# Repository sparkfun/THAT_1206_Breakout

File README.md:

SparkFun THAT 1206 Breakout
========================================

[*BOB-14002*](https://www.sparkfun.com/products/14002)

The SparkFun THAT 1206 InGenius Breakout Board offers an easy solution to adding a balanced audio input to your circuits. The THAT InGenius technology has been designed for high-grade analog line receiving and offers a low distortion and high common mode rejection in real-world audio applications. Each breakout board combines the THAT 1206 IC, its supporting components, and a ¼" TRS (Tip Ring Sleeve) socket. With these powers combined, you will find it very easy to use the input drivers on breadboards and in projects!

The THAT 1206 InGenius Breakout and its sibling, the THAT 1646 OutSmarts Breakout, perform mirror-image signal conversion. While the OutSmarts is an unbalanced-to-balanced output driver, this InGenius is a balanced-to-unbalanced input receiver. We have made sure to break out each pin you need to utilize the InGenius board, including the unbalanced output (OUT), the positive and negative power supply rails (V+, V-) and, of course, ground (GND). Additionally, adjacent to each leg of the socket are test points for the signal (T, R, S) and normal (TN, RN, SN) contacts.

Repository Contents
-------------------

* **/Hardware** - Eagle design files (.brd, .sch)
* **/Production** - Production panel files (.brd)

Documentation
--------------
* **[Hookup Guide](https://learn.sparkfun.com/tutorials/that-ingenuis-and-outsmarts-breakout-hookup-guide)** - Basic hookup guide for the THAT 1206 and 1646 breakouts.
* **[SparkFun Fritzing repo](https://github.com/sparkfun/Fritzing_Parts)** - Fritzing diagrams for SparkFun products.
* **[SparkFun 3D Model repo](https://github.com/sparkfun/3D_Models)** - 3D models of SparkFun products.

Product Versions
----------------
* [BOB-14002](https://www.sparkfun.com/products/14002) - THAT 1206 InGenius breakout board.
* [BOB-14003](https://www.sparkfun.com/products/14003) - The companion THAT 1646 OutSmarts breakout board.

Version History
---------------
* [V1.0 Tag](https://github.com/sparkfun/THAT_1206_Breakout/commit/8fa3e24b62fe93f8f912508c355df1751a37f655) - Files as of product launch.

License Information
-------------------

This product is _**open source**_!

Please review the LICENSE.md file for license information.

If you have any questions or concerns on licensing, please contact techsupport@sparkfun.com.

Distributed as-is; no warranty is given.

- Your friends at SparkFun.

_<COLLABORATION CREDIT>_

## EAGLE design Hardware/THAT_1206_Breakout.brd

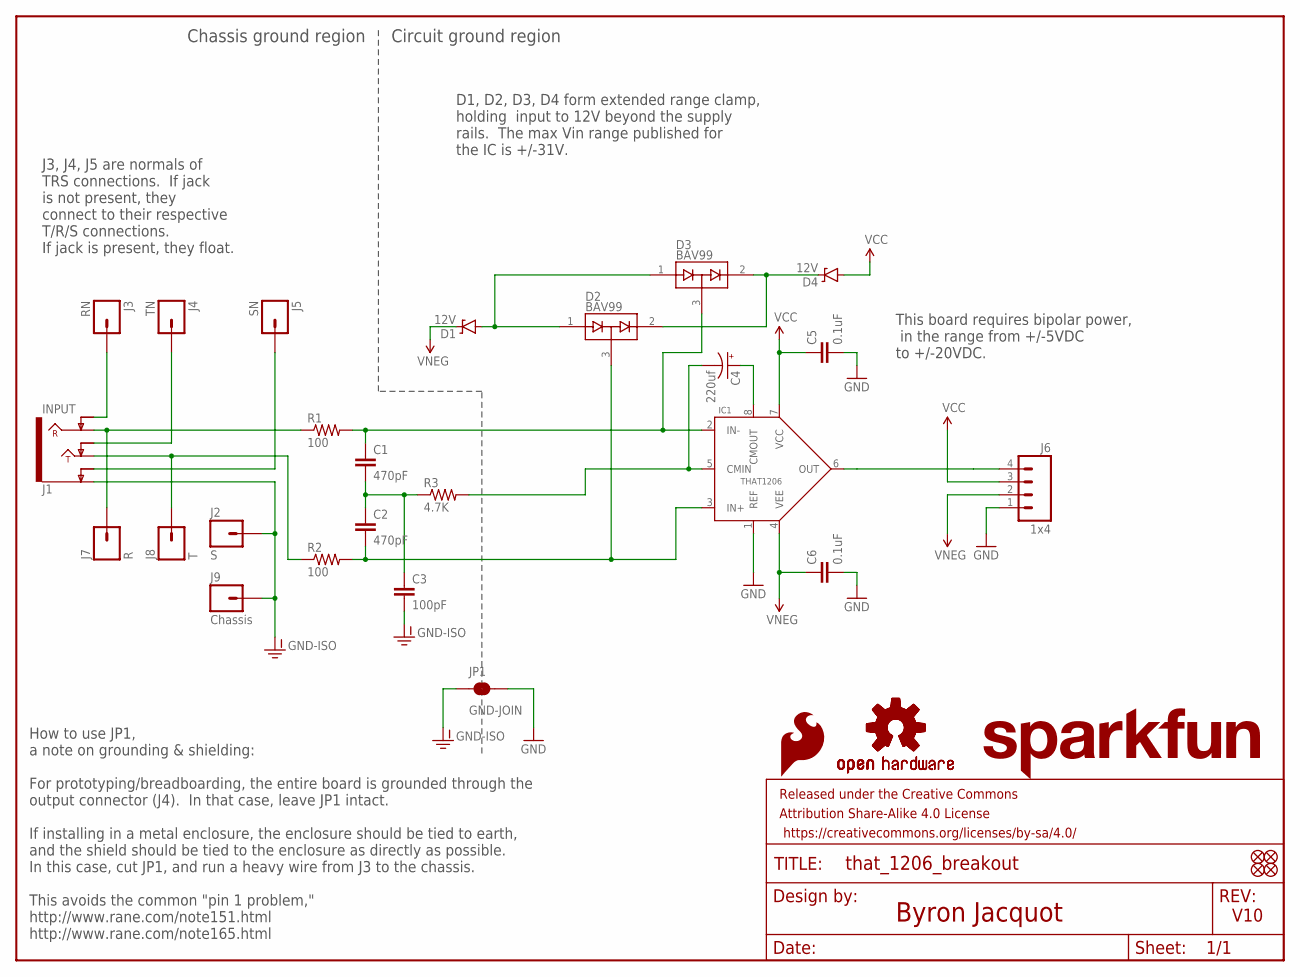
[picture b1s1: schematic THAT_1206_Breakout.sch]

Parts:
C1, C2: 470pF; 0603-CAP
C3: 100pF; 0603-CAP
C4: 220uf; PANASONIC_D
C5, C6: 0.1uF; 0603-CAP
D1, D4: 12V; SOD-323
D2, D3: BAV99; SOT23-3
FD1, FD2, FD3, FD4: FIDUCIALUFIDUCIAL; MICRO-FIDUCIAL
FRAME1: FRAME-LETTER; CREATIVE_COMMONS
IC1: THAT1206; SO08
J1: INPUT; AUDIO_JACK_0.25"_TRS_PTH_RA
J2: S; 1X01_NO_SILK
J3: RN; 1X01_NO_SILK
J4: TN; 1X01_NO_SILK
J5: SN; 1X01_NO_SILK
J6: 1x4; 1X04_NO_SILK_ALL_ROUND
J7: R; 1X01_NO_SILK
J8: T; 1X01_NO_SILK
J9: Chassis; 1X01_NO_SILK
JP1: GND-JOIN; PAD-JUMPER-2-NC_BY_TRACE_YES_SILK
LOGO2: SFE_LOGO_FLAME.2_INCH; SFE_LOGO_FLAME_.2
LOGO3, LOGO4: OSHW-LOGOS; OSHW-LOGO-S
LOGO5: SFE_LOGO_NAME.1_INCH; SFE_LOGO_NAME_.1
R1, R2: 100; 0603-RES
R3: 4.7K; 0603-RES

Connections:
GND: C5.2, C6.2, IC1.1 (REF), J6.1, JP1.2
GND-ISO: C3.2, J1.SLEEVE (EARTH), J2.1, J9.1, JP1.1
unnamed: J1.RING, J7.1, R1.1
unnamed: C1.1, D3.3 (COM), IC1.2 (IN-), R1.2
unnamed: J1.TIP, J8.1, R2.1
unnamed: C2.2, D2.3 (COM), IC1.3 (IN+), R2.2
unnamed: C1.2, C2.1, C3.1, R3.1
unnamed: C4.-, IC1.5 (CMIN), R3.2
unnamed: C4.+, IC1.8 (CMOUT)
unnamed: J1.SLEEVE-NORM (EARTH-NORM), J5.1
unnamed: J1.TIP-NORM, J4.1
unnamed: J1.RING-NORM, J3.1
unnamed: D1.A, D2.1 (A1), D3.1 (A1)
unnamed: D2.2 (C2), D3.2 (C2), D4.C
RCV: IC1.6 (OUT), J6.4
VCC: C5.1, D4.A, IC1.7 (VCC), J6.3
VNEG: C6.1, D1.C, IC1.4 (VEE), J6.2

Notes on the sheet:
Byron Jacquot
V10
How to use JP1, a note on grounding & shielding: For prototyping/breadboarding, the entire board is grounded through the output connector (J4). In that case, leave JP1 intact. If installing in a metal enclosure, the enclosure should be tied to earth, and the shield should be tied to the enclosure a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
This board requires bipolar power, in the range from +/-5VDC to +/-20VDC.
Chassis ground region
Circuit ground region
D1, D2, D3, D4 form extended range clamp, holding input to 12V beyond the supply rails. The max Vin range published for the IC is +/-31V.
J3, J4, J5 are normals of TRS connections. If jack is not present, they connect to their respective T/R/S connections. If jack is present, they float.

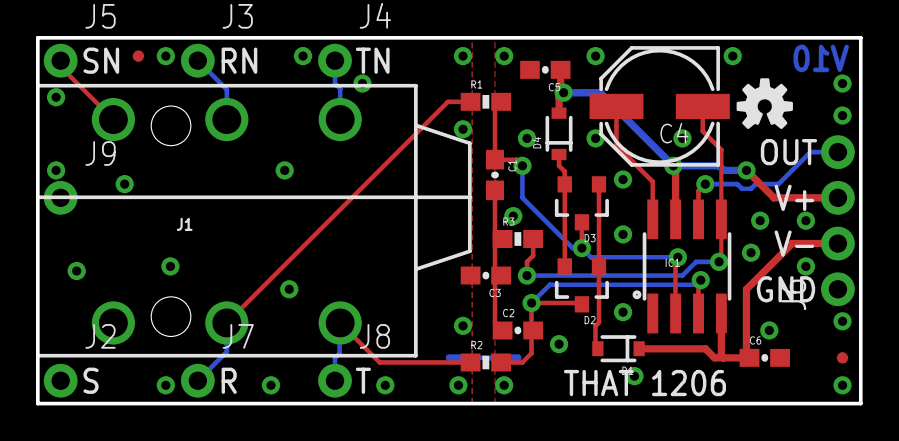
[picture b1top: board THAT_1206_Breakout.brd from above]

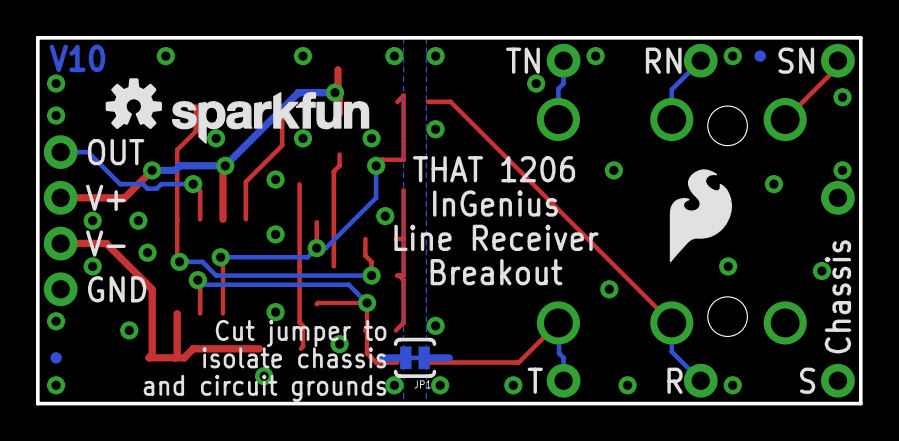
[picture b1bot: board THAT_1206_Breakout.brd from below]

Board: 2 copper layers, 45.7 x 20.3 mm, 33 parts (6 on the bottom side), 17 nets.

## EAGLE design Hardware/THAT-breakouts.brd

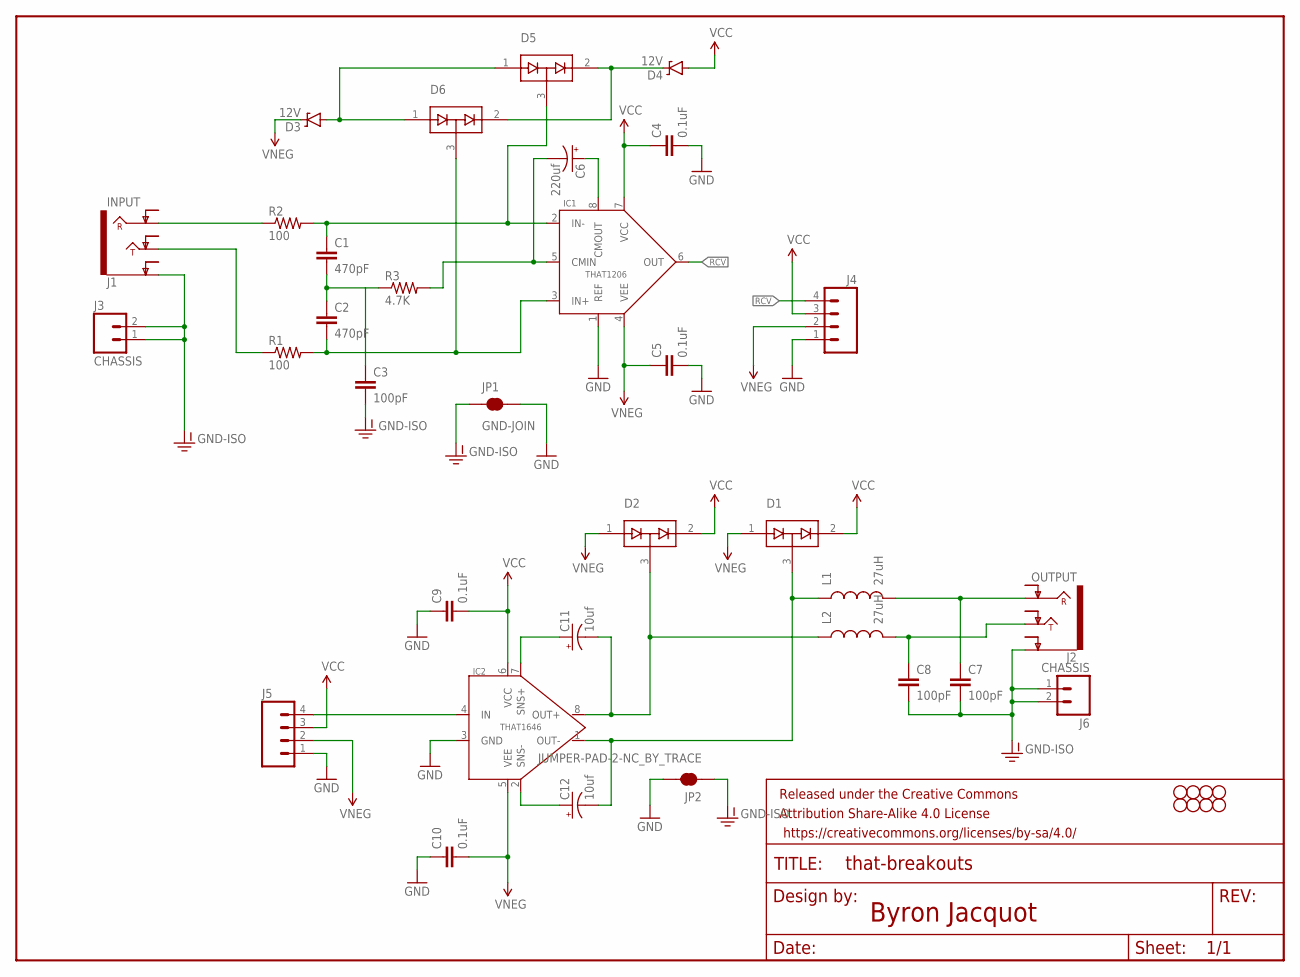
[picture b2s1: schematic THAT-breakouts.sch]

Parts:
C1, C2: 470pF; 0603-CAP
C3, C7, C8: 100pF; 0603-CAP
C4, C5, C9, C10: 0.1uF; 0603-CAP
C6: 220uf; PANASONIC_D
C11, C12: 10uf; PANASONIC_D
D1, D2, D5, D6: BAV99; SOT23-3
D3, D4: 12V; SOD-323
FRAME1: FRAME-LETTER; CREATIVE_COMMONS
H1, H2, H3, H4, H5, H6, H7, H8: STAND-OFF
IC1: THAT1206; SO08
IC2: THAT1646; SO08
J1: INPUT; AUDIO-JACK-.25-INCH-HORIZ-PTH
J2: OUTPUT; AUDIO-JACK-.25-INCH-HORIZ-PTH
J3, J6: CHASSIS; 1X02_NO_SILK
J4, J5: M04NO_SILK_ALL_ROUND; 1X04_NO_SILK_ALL_ROUND
JP1: GND-JOIN; PAD-JUMPER-2-NC_BY_TRACE_YES_SILK
JP2: JUMPER-PAD-2-NC_BY_TRACE; PAD-JUMPER-2-NC_BY_TRACE_YES_SILK
L1, L2: 27uH; 0603
R1, R2: 100; 0603-RES
R3: 4.7K; 0603-RES

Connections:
GND: C4.2, C5.2, C9.1, C10.1, IC1.1 (REF), IC2.3 (GND), J4.1, J5.1, JP1.2, JP2.2
GND-ISO: C3.2, C7.2, C8.2, J1.SLEEVE (EARTH), J2.SLEEVE (EARTH), J3.1, J3.2, J6.1, J6.2, JP1.1, JP2.1
unnamed: J1.RING, R2.1
unnamed: C1.1, D5.3 (COM), IC1.2 (IN-), R2.2
unnamed: J1.TIP, R1.1
unnamed: C2.2, D6.3 (COM), IC1.3 (IN+), R1.2
unnamed: C1.2, C2.1, C3.1, R3.1
unnamed: C6.-, IC1.5 (CMIN), R3.2
unnamed: C6.+, IC1.8 (CMOUT)
unnamed: C8.1, J2.TIP, L2.2
unnamed: C7.1, J2.RING, L1.2
unnamed: C11.-, D2.3 (COM), IC2.8 (OUT+), L2.1
unnamed: C12.-, D1.3 (COM), IC2.1 (OUT-), L1.1
unnamed: D3.A, D5.1 (A1), D6.1 (A1)
unnamed: C12.+, IC2.2 (SNS-)
unnamed: C11.+, IC2.7 (SNS+)
unnamed: D4.C, D5.2 (C2), D6.2 (C2)
unnamed: IC2.4 (IN), J5.4
RCV: IC1.6 (OUT), J4.4
VCC: C4.1, C9.2, D1.2 (C2), D2.2 (C2), D4.A, IC1.7 (VCC), IC2.6 (VCC), J4.3, J5.3
VNEG: C5.1, C10.2, D1.1 (A1), D2.1 (A1), D3.C, IC1.4 (VEE), IC2.5 (VEE), J4.2, J5.2

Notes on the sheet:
Byron Jacquot

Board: 2 copper layers, 42 parts (2 on the bottom side), 21 nets, no tracks yet.

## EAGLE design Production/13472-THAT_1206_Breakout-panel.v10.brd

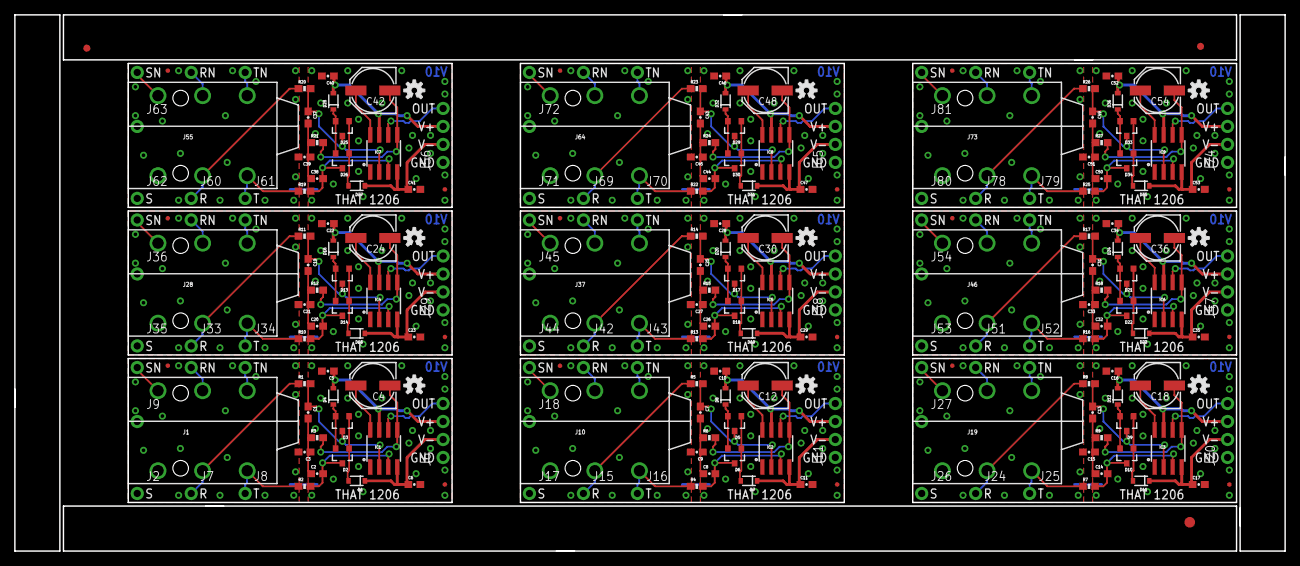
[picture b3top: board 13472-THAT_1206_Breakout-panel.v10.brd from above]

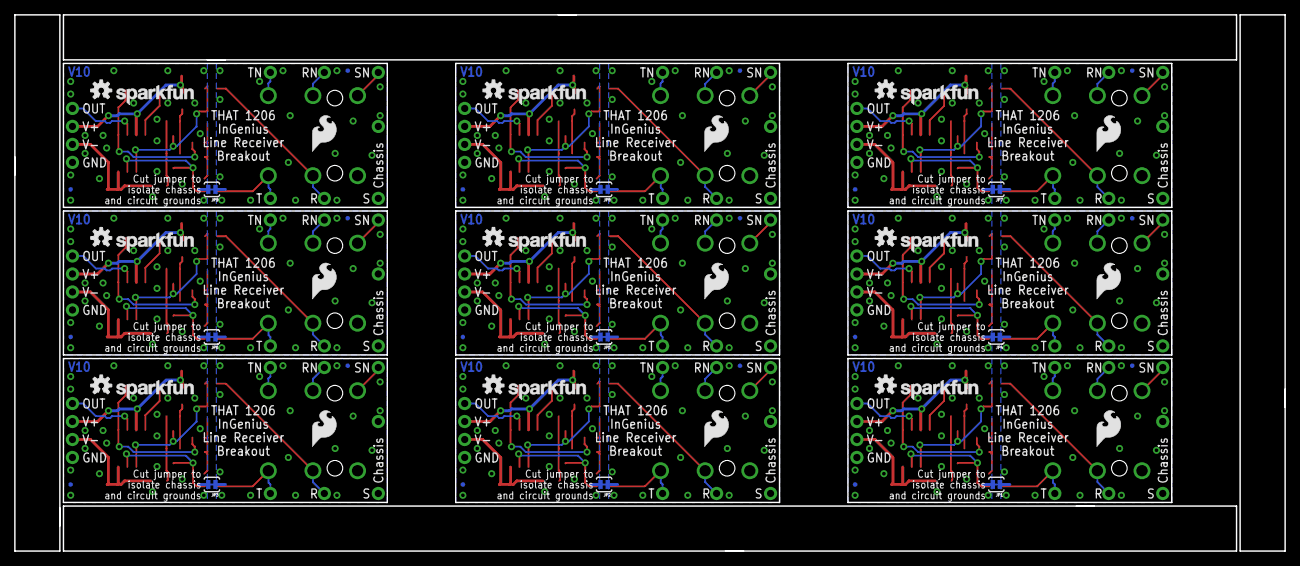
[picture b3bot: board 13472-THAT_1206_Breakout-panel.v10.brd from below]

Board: 2 copper layers, 179.3 x 75.7 mm, 291 parts (54 on the bottom side), 153 nets.

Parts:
C1, C2, C7, C8, C13, C14, C19, C20, C25, C26, C31, C32, C37, C38, C43, C44, C49, C50: 470pF; 0603-CAP
C3, C9, C15, C21, C27, C33, C39, C45, C51: 100pF; 0603-CAP
C4, C12, C18, C24, C30, C36, C42, C48, C54: 220uf; PANASONIC_D
C5, C6, C10, C11, C16, C17, C22, C23, C28, C29, C34, C35, C40, C41, C46, C47, C52, C53: 0.1uF; 0603-CAP
D1, D4, D7, D8, D11, D12, D15, D16, D19, D20, D23, D24, D27, D28, D31, D32, D35, D36: 12V; SOD-323
D2, D3, D5, D6, D9, D10, D13, D14, D17, D18, D21, D22, D25, D26, D29, D30, D33, D34: BAV99; SOT23-3
E$1: FIDUCIAL-1.5X3
E$7, E$8: FIDUCIAL-1X2
FD1, FD2, FD3, FD4, FD5, FD6, FD7, FD8, FD9, FD10, FD11, FD12, FD13, FD14, FD15, FD16, FD17, FD18, FD19, FD20, FD21, FD22, FD23, FD24, FD25, FD26, FD27, FD28, FD29, FD30, FD31, FD32, FD33, FD34, FD35, FD36: FIDUCIALUFIDUCIAL; MICRO-FIDUCIAL
IC1, IC2, IC3, IC4, IC5, IC6, IC7, IC8, IC9: THAT1206; SO08
J1, J10, J19, J28, J37, J46, J55, J64, J73: INPUT; AUDIO_JACK_0.25"_TRS_PTH_RA
J2, J17, J26, J35, J44, J53, J62, J71, J80: S; 1X01_NO_SILK
J3, J12, J21, J30, J39, J48, J57, J66, J75: RN; 1X01_NO_SILK
J4, J13, J22, J31, J40, J49, J58, J67, J76: TN; 1X01_NO_SILK
J5, J14, J23, J32, J41, J50, J59, J68, J77: SN; 1X01_NO_SILK
J6, J11, J20, J29, J38, J47, J56, J65, J74: 1x4; 1X04_NO_SILK_ALL_ROUND
J7, J15, J24, J33, J42, J51, J60, J69, J78: R; 1X01_NO_SILK
J8, J16, J25, J34, J43, J52, J61, J70, J79: T; 1X01_NO_SILK
J9, J18, J27, J36, J45, J54, J63, J72, J81: Chassis; 1X01_NO_SILK
JP1, JP2, JP3, JP4, JP5, JP6, JP7, JP8, JP9: GND-JOIN; PAD-JUMPER-2-NC_BY_TRACE_YES_SILK
LOGO1, LOGO3, LOGO4, LOGO6, LOGO9, LOGO10, LOGO13, LOGO14, LOGO17, LOGO18, LOGO21, LOGO22, LOGO25, LOGO26, LOGO29, LOGO30, LOGO33, LOGO34: OSHW-LOGOS; OSHW-LOGO-S
LOGO2, LOGO7, LOGO11, LOGO15, LOGO19, LOGO23, LOGO27, LOGO31, LOGO35: SFE_LOGO_FLAME.2_INCH; SFE_LOGO_FLAME_.2
LOGO5, LOGO8, LOGO12, LOGO16, LOGO20, LOGO24, LOGO28, LOGO32, LOGO36: SFE_LOGO_NAME.1_INCH; SFE_LOGO_NAME_.1
R1, R2, R4, R5, R7, R8, R10, R11, R13, R14, R16, R17, R19, R20, R22, R23, R25, R26: 100; 0603-RES
R3, R6, R9, R12, R15, R18, R21, R24, R27: 4.7K; 0603-RES

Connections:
GND: C5.2, C6.2, IC1.1, J6.1, JP1.2
GND1: C10.2, C11.2, IC2.1, J11.1, JP2.2
GND2: C16.2, C17.2, IC3.1, J20.1, JP3.2
GND3: C22.2, C23.2, IC4.1, J29.1, JP4.2
GND4: C28.2, C29.2, IC5.1, J38.1, JP5.2
GND5: C34.2, C35.2, IC6.1, J47.1, JP6.2
GND6: C40.2, C41.2, IC7.1, J56.1, JP7.2
GND7: C46.2, C47.2, IC8.1, J65.1, JP8.2
GND8: C52.2, C53.2, IC9.1, J74.1, JP9.2
GND-ISO: C3.2, J1.SLEEVE, J2.1, J9.1, JP1.1
GND-ISO1: C9.2, J10.SLEEVE, J17.1, J18.1, JP2.1
GND-ISO2: C15.2, J19.SLEEVE, J26.1, J27.1, JP3.1
GND-ISO3: C21.2, J28.SLEEVE, J35.1, J36.1, JP4.1
GND-ISO4: C27.2, J37.SLEEVE, J44.1, J45.1, JP5.1
GND-ISO5: C33.2, J46.SLEEVE, J53.1, J54.1, JP6.1
GND-ISO6: C39.2, J55.SLEEVE, J62.1, J63.1, JP7.1
GND-ISO7: C45.2, J64.SLEEVE, J71.1, J72.1, JP8.1
GND-ISO8: C51.2, J73.SLEEVE, J80.1, J81.1, JP9.1
unnamed: J1.RING, J7.1, R1.1
unnamed: C1.1, D3.3, IC1.2, R1.2
unnamed: J1.TIP, J8.1, R2.1
unnamed: C2.2, D2.3, IC1.3, R2.2
unnamed: C1.2, C2.1, C3.1, R3.1
unnamed: C4.-, IC1.5, R3.2
unnamed: C4.+, IC1.8
unnamed: J1.SLEEVE-NORM, J5.1
unnamed: J1.TIP-NORM, J4.1
unnamed: J1.RING-NORM, J3.1
unnamed: J10.RING, J15.1, R5.1
unnamed: D1.A, D2.1, D3.1
unnamed: C7.1, D5.3, IC2.2, R5.2
unnamed: J10.TIP, J16.1, R4.1
unnamed: D2.2, D3.2, D4.C
unnamed: C8.2, D6.3, IC2.3, R4.2
unnamed: C7.2, C8.1, C9.1, R6.1
unnamed: C12.-, IC2.5, R6.2
unnamed: C12.+, IC2.8
unnamed: D5.1, D6.1, D7.A
unnamed: D5.2, D6.2, D8.C
unnamed: J10.SLEEVE-NORM, J14.1
unnamed: J10.TIP-NORM, J13.1
unnamed: J10.RING-NORM, J12.1
unnamed: J19.RING, J24.1, R8.1
unnamed: C13.1, D9.3, IC3.2, R8.2
unnamed: J19.TIP, J25.1, R7.1
unnamed: C14.2, D10.3, IC3.3, R7.2
unnamed: C13.2, C14.1, C15.1, R9.1
unnamed: C18.-, IC3.5, R9.2
unnamed: C18.+, IC3.8
unnamed: D9.1, D10.1, D11.A
unnamed: D9.2, D10.2, D12.C
unnamed: J19.SLEEVE-NORM, J23.1
unnamed: J19.TIP-NORM, J22.1
unnamed: J19.RING-NORM, J21.1
unnamed: J28.RING, J33.1, R11.1
unnamed: C19.1, D13.3, IC4.2, R11.2
unnamed: J28.TIP, J34.1, R10.1
unnamed: C20.2, D14.3, IC4.3, R10.2
unnamed: C19.2, C20.1, C21.1, R12.1
unnamed: C24.-, IC4.5, R12.2
unnamed: C24.+, IC4.8
unnamed: D13.1, D14.1, D15.A
unnamed: D13.2, D14.2, D16.C
unnamed: J28.SLEEVE-NORM, J32.1
unnamed: J28.TIP-NORM, J31.1
unnamed: J28.RING-NORM, J30.1
unnamed: J37.RING, J42.1, R14.1
unnamed: C25.1, D17.3, IC5.2, R14.2
unnamed: J37.TIP, J43.1, R13.1
unnamed: C26.2, D18.3, IC5.3, R13.2
unnamed: C25.2, C26.1, C27.1, R15.1
unnamed: C30.-, IC5.5, R15.2
unnamed: C30.+, IC5.8
unnamed: D17.1, D18.1, D19.A
unnamed: D17.2, D18.2, D20.C
unnamed: J37.SLEEVE-NORM, J41.1
unnamed: J37.TIP-NORM, J40.1
unnamed: J37.RING-NORM, J39.1
unnamed: J46.RING, J51.1, R17.1
unnamed: C31.1, D21.3, IC6.2, R17.2
unnamed: J46.TIP, J52.1, R16.1
unnamed: C32.2, D22.3, IC6.3, R16.2
unnamed: C31.2, C32.1, C33.1, R18.1
unnamed: C36.-, IC6.5, R18.2
unnamed: C36.+, IC6.8
unnamed: D21.1, D22.1, D23.A
unnamed: D21.2, D22.2, D24.C
unnamed: J46.SLEEVE-NORM, J50.1
unnamed: J46.TIP-NORM, J49.1
unnamed: J46.RING-NORM, J48.1
unnamed: J55.RING, J60.1, R20.1
unnamed: C37.1, D25.3, IC7.2, R20.2
unnamed: J55.TIP, J61.1, R19.1
unnamed: C38.2, D26.3, IC7.3, R19.2
unnamed: C37.2, C38.1, C39.1, R21.1
unnamed: C42.-, IC7.5, R21.2
unnamed: C42.+, IC7.8
unnamed: D25.1, D26.1, D27.A
unnamed: D25.2, D26.2, D28.C
unnamed: J55.SLEEVE-NORM, J59.1
unnamed: J55.TIP-NORM, J58.1
unnamed: J55.RING-NORM, J57.1
unnamed: J64.RING, J69.1, R23.1
unnamed: C43.1, D29.3, IC8.2, R23.2
unnamed: J64.TIP, J70.1, R22.1
unnamed: C44.2, D30.3, IC8.3, R22.2
unnamed: C43.2, C44.1, C45.1, R24.1
unnamed: C48.-, IC8.5, R24.2
unnamed: C48.+, IC8.8
unnamed: D29.1, D30.1, D31.A
unnamed: D29.2, D30.2, D32.C
unnamed: J64.SLEEVE-NORM, J68.1
unnamed: J64.TIP-NORM, J67.1
unnamed: J64.RING-NORM, J66.1
unnamed: J73.RING, J78.1, R26.1
unnamed: C49.1, D33.3, IC9.2, R26.2
unnamed: J73.TIP, J79.1, R25.1
unnamed: C50.2, D34.3, IC9.3, R25.2
unnamed: C49.2, C50.1, C51.1, R27.1
unnamed: C54.-, IC9.5, R27.2
unnamed: C54.+, IC9.8
unnamed: D33.1, D34.1, D35.A
unnamed: D33.2, D34.2, D36.C
unnamed: J73.SLEEVE-NORM, J77.1
unnamed: J73.TIP-NORM, J76.1
unnamed: J73.RING-NORM, J75.1
RCV: IC1.6, J6.4
RCV1: IC2.6, J11.4
RCV2: IC3.6, J20.4
RCV3: IC4.6, J29.4
RCV4: IC5.6, J38.4
RCV5: IC6.6, J47.4
RCV6: IC7.6, J56.4
RCV7: IC8.6, J65.4
RCV8: IC9.6, J74.4
VCC: C5.1, D4.A, IC1.7, J6.3
VCC1: C10.1, D8.A, IC2.7, J11.3
VCC2: C16.1, D12.A, IC3.7, J20.3
VCC3: C22.1, D16.A, IC4.7, J29.3
VCC4: C28.1, D20.A, IC5.7, J38.3
VCC5: C34.1, D24.A, IC6.7, J47.3
VCC6: C40.1, D28.A, IC7.7, J56.3
VCC7: C46.1, D32.A, IC8.7, J65.3
VCC8: C52.1, D36.A, IC9.7, J74.3
VNEG: C6.1, D1.C, IC1.4, J6.2
VNEG1: C11.1, D7.C, IC2.4, J11.2
VNEG2: C17.1, D11.C, IC3.4, J20.2
VNEG3: C23.1, D15.C, IC4.4, J29.2
VNEG4: C29.1, D19.C, IC5.4, J38.2
VNEG5: C35.1, D23.C, IC6.4, J47.2
VNEG6: C41.1, D27.C, IC7.4, J56.2
VNEG7: C47.1, D31.C, IC8.4, J65.2
VNEG8: C53.1, D35.C, IC9.4, J74.2

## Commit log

2016-07-07 Committing boilerplate from repo template.
2016-07-07 Initial tinkering with the idea.
2016-07-08 More WIP & conceptual work.
2016-07-09 Still more WIP.
2016-07-21 Found some zeners...
2016-07-26 Broke into 2 separate board files.
2016-07-27 Moved 1646 to its own repo.
2016-07-27 Routed PCB.
2016-07-27 Updates after routing.
    Added ground stitches & dimensions.
2016-08-08 After proto review.
    Many fit & finish changes.
2016-08-08 Fixing the nonpolar caps
    To have non-polarized schem symbols, and adding PROD_IDs.
2016-08-09 Ran engineering checklist, a few small changes.
2016-08-09 Fixing text in schem.
2016-08-09 Fixing Kade's checklist issues.
    -Un-"toed."
    -Moved chassis ground connection.
2017-01-09 Adding testpoints on T/R/S connections.
2017-01-09 Moving PTH holes to 0.1" grid, matching size to 1646 board.
2017-01-16 Updating .gitignore to ignore spice temp files.
2017-01-16 Updates after group review.
    -Chassis ground moved out of selective solder runout path.
    -Flame turned right side up.
    -A few via/silk overlaps fixed.
2017-01-16 Updated after running checklist.
    Biggest change is that TRS jack was updated with new libraries.
2017-01-17 Found under-spec silk widths on the new caps and ICs.
2017-01-27 panel
2017-03-31 Release checkin.
    Removing unused subdirectories.
    Updating README.
2017-03-31 Fixing mistake in jumper numbering in schem info.
    J9 is the one to use for grounding!

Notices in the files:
parts and their libraries:
SparkFun-DiscreteSemi: Licensing: Creative Commons ShareAlike 4.0 International - https://creativecommons.org/licenses/by-sa/4.0
SparkFun-Aesthetics: Released under the Creative Commons Attribution Share-Alike 4.0 License
SparkFun-Aesthetics: https://creativecommons.org/licenses/by-sa/4.0
